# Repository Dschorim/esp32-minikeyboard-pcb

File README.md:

# esp32-minikeyboard-pcb
PCB design files for 2x2 keyboard with esp32

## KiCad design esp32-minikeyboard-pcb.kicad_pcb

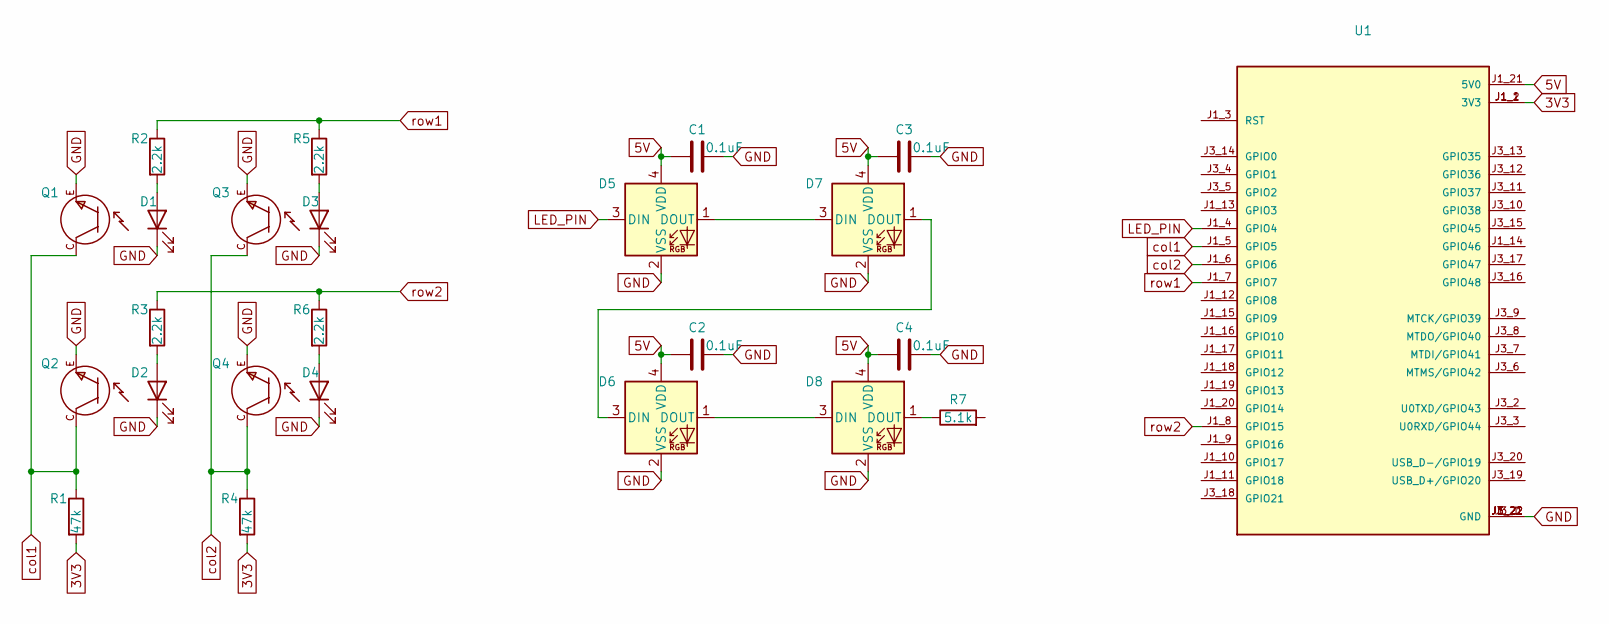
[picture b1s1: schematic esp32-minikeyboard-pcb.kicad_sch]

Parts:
C1, C2, C3, C4: 0.1uF; C_0603_1608Metric
D1, D2, D3, D4: IR12-21C; LED_IR12-21C_TR8
D5, D6, D7, D8: SK6805; LED_SK6805_PLCC4_2.4x2.7mm_P1.3mm
Q1, Q2, Q3, Q4: PT12-21C/TR8; TRANS_PT12-21C_TR8; PARTREV 4
R1, R4: 47k; R_0603_1608Metric
R2, R3, R5, R6: 2.2k; R_0603_1608Metric
R7: 5.1k; R_0603_1608Metric
U1: ESP32-S3-DEVKITC-1-N8R2; XCVR_ESP32-S3-DEVKITC-1-N8R2; PARTREV V1

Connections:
3V3: R1.2, R4.2, U1.J1_1 (3V3), U1.J1_2 (3V3)
5V: C1.1, C2.1, C3.1, C4.1, D5.4 (VDD), D6.4 (VDD), D7.4 (VDD), D8.4 (VDD), U1.J1_21 (5V0)
GND: C1.2, C2.2, C3.2, C4.2, D1.K, D2.K, D3.K, D4.K, D5.2 (VSS), D6.2 (VSS), D7.2 (VSS), D8.2 (VSS), Q1.E, Q2.E, Q3.E, Q4.E, U1.J1_22 (GND), U1.J3_1 (GND), U1.J3_21 (GND), U1.J3_22 (GND)
LED_PIN: D5.3 (DIN), U1.J1_4 (GPIO4)
unnamed: D1.A, R2.2
unnamed: D2.A, R3.2
unnamed: D3.A, R5.2
unnamed: D4.A, R6.2
unnamed: D5.1 (DOUT), D7.3 (DIN)
unnamed: D6.1 (DOUT), D8.3 (DIN)
unnamed: D6.3 (DIN), D7.1 (DOUT)
unnamed: D8.1 (DOUT), R7.1
col1: Q1.C, Q2.C, R1.1, U1.J1_5 (GPIO5)
col2: Q3.C, Q4.C, R4.1, U1.J1_6 (GPIO6)
row1: R2.1, R5.1, U1.J1_7 (GPIO7)
row2: R3.1, R6.1, U1.J1_8 (GPIO15)

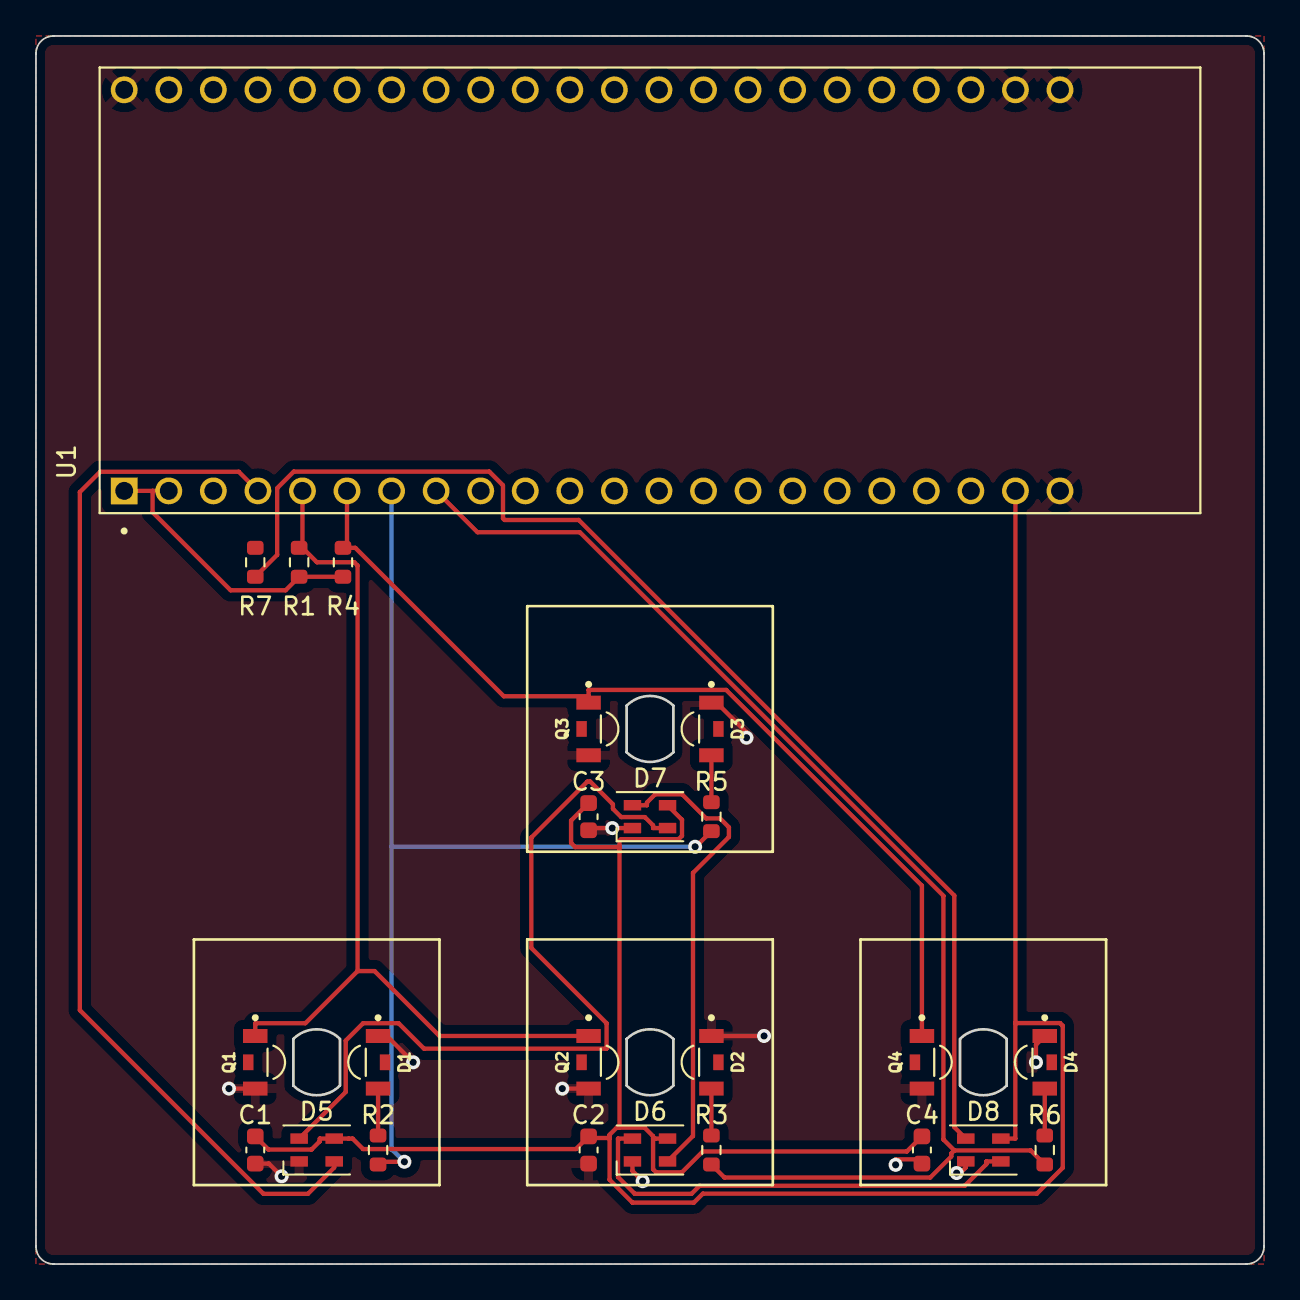
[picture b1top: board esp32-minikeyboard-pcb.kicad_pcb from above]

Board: 2 copper layers, 69.9 x 69.9 mm, 24 parts (0 on the bottom side), 16 nets.

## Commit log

2022-08-24 added matrix
2022-08-25 finished design
